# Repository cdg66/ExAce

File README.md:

# 📘 Project ExAce

> [!Warning]
>
> Content is not proven and suject to change without notice! Send to fab at your own risk. 

## 🧩 Overview

A tiny yet powerful fpga acceleration card designed with the Framework laptop expansion module system in mind.

## 🛠️ Features

- ✅ [CCGM1A1/2/4 compatible](https://colognechip.com/docs/ds1001-gatemate1-datasheet-latest.pdf)
- ✅ 20,480, 40,960 or 81,920 8-input LUT-trees.
- ✅ USB-type C, 5V 1.5A.
- ✅ Full access to SERDES via the USB-c connector (1 for A1/A2 and 2 for A4 device).
- ✅ USB2.0 interface is shared between the fpga and mcu via a USB mux.
- ✅ STM32L422RBI6 coprocessor and programmer.
- ✅ Shared Earth and i2c between the fpga and microcontroller for easier development.
- ✅ Free and Open-source FPGA toolchain!
- ✅ Lots of sensors!: PDM microphone, 6DoF imu, magnetometer, and thermometer.
- ✅ 8 user programmable led ideal for VU meters.
- ✅ 1 lvds IO ideal for connecting multiple board together in a cluster.
- 🔜 TinyFPGA-Bootloader support TBD.
- 🔜 DirtyJTAG support TBD.

---

## 💪 Application

- ✅ Machine learning
- ✅ Simulation
- ✅ Audio/Signal processing
- ✅ Retro Gaming
- ✅ Development platform

## 🗂️ Repository Structure

```bash
📁 /pcb-project-root
├── /3D_Models                    # 3D models of the PCB rendering
├── /Outputs/Fabrication          # Generated Gerber files, BOM and POS for fabrication
├── /PINOUT                       # STM32CubeMx for reference pinout
├── /Testbench/ExAceTestbench     # Testbench to break out serdes signals
├── /.gitignore
└── README.md
```

---

## 🧰 Tools & Dependencies

- **Design Software:** KiCad (v9.0.2 or higher)
- **MCU/FPGA Programmer:** ST-Link,Pico Dirty JTAG
- **Firmware Toolchain:** STM32CubeMX, arm toolchain, [Colonge chip open source toolchain](https://www.colognechip.com/docs/ug1002-toolchain-install-latest.pdf)  

---

## 🖼️ 3D view

---

## 🏗️ Getting Started

1. **Clone this repository**
   ```bash
   git clone https://github.com/cdg66/ExAce.git
   ```
2. **Open the project** in KiCad (navigate to `Expansion_Card_Retrofit.kicad_pro`)
3. **Modify / Build / Export Gerbers**

---

## 🚀 Fabrication

To get the board fabricated:

- Use the files in the `/Outputs` directory
- Recommended fabs:
  - [NextPcb](https://www.nextpcb.com/)
  - [JLCPCB](https://jlcpcb.com/) 

Stack-up:

The recommended stack up is the JLC08081H-1080A at JLCPCB but can be done at any other PCB manufacturer.

---

## 🔧 License

This work is licensed under a [Creative Commons Attribution 4.0 International License](https://creativecommons.org/licenses/by/4.0/).

This project references and builds upon the open-source designs from  
[FrameworkComputer/ExpansionCards](https://github.com/FrameworkComputer/ExpansionCards),  
which is also licensed under the [Creative Commons Attribution 4.0 International License (CC-BY-4.0)](https://creativecommons.org/licenses/by/4.0/).

TPSM82822SILR

Footprint: Ultralibrarian

3D model: SnapMagic

Edited by me

S3A2505-100.000-L-X1-R

Symbol, Footprint, 3D model: SnapMagic

Edited by me

1054440011

3D model: Molex

KXT_331_LHS

3D model: SnapMagic

STM32L422RBI6

3D model: SnapMagic

TPS7A2033PDQNR

3D model: SnapMagic

---

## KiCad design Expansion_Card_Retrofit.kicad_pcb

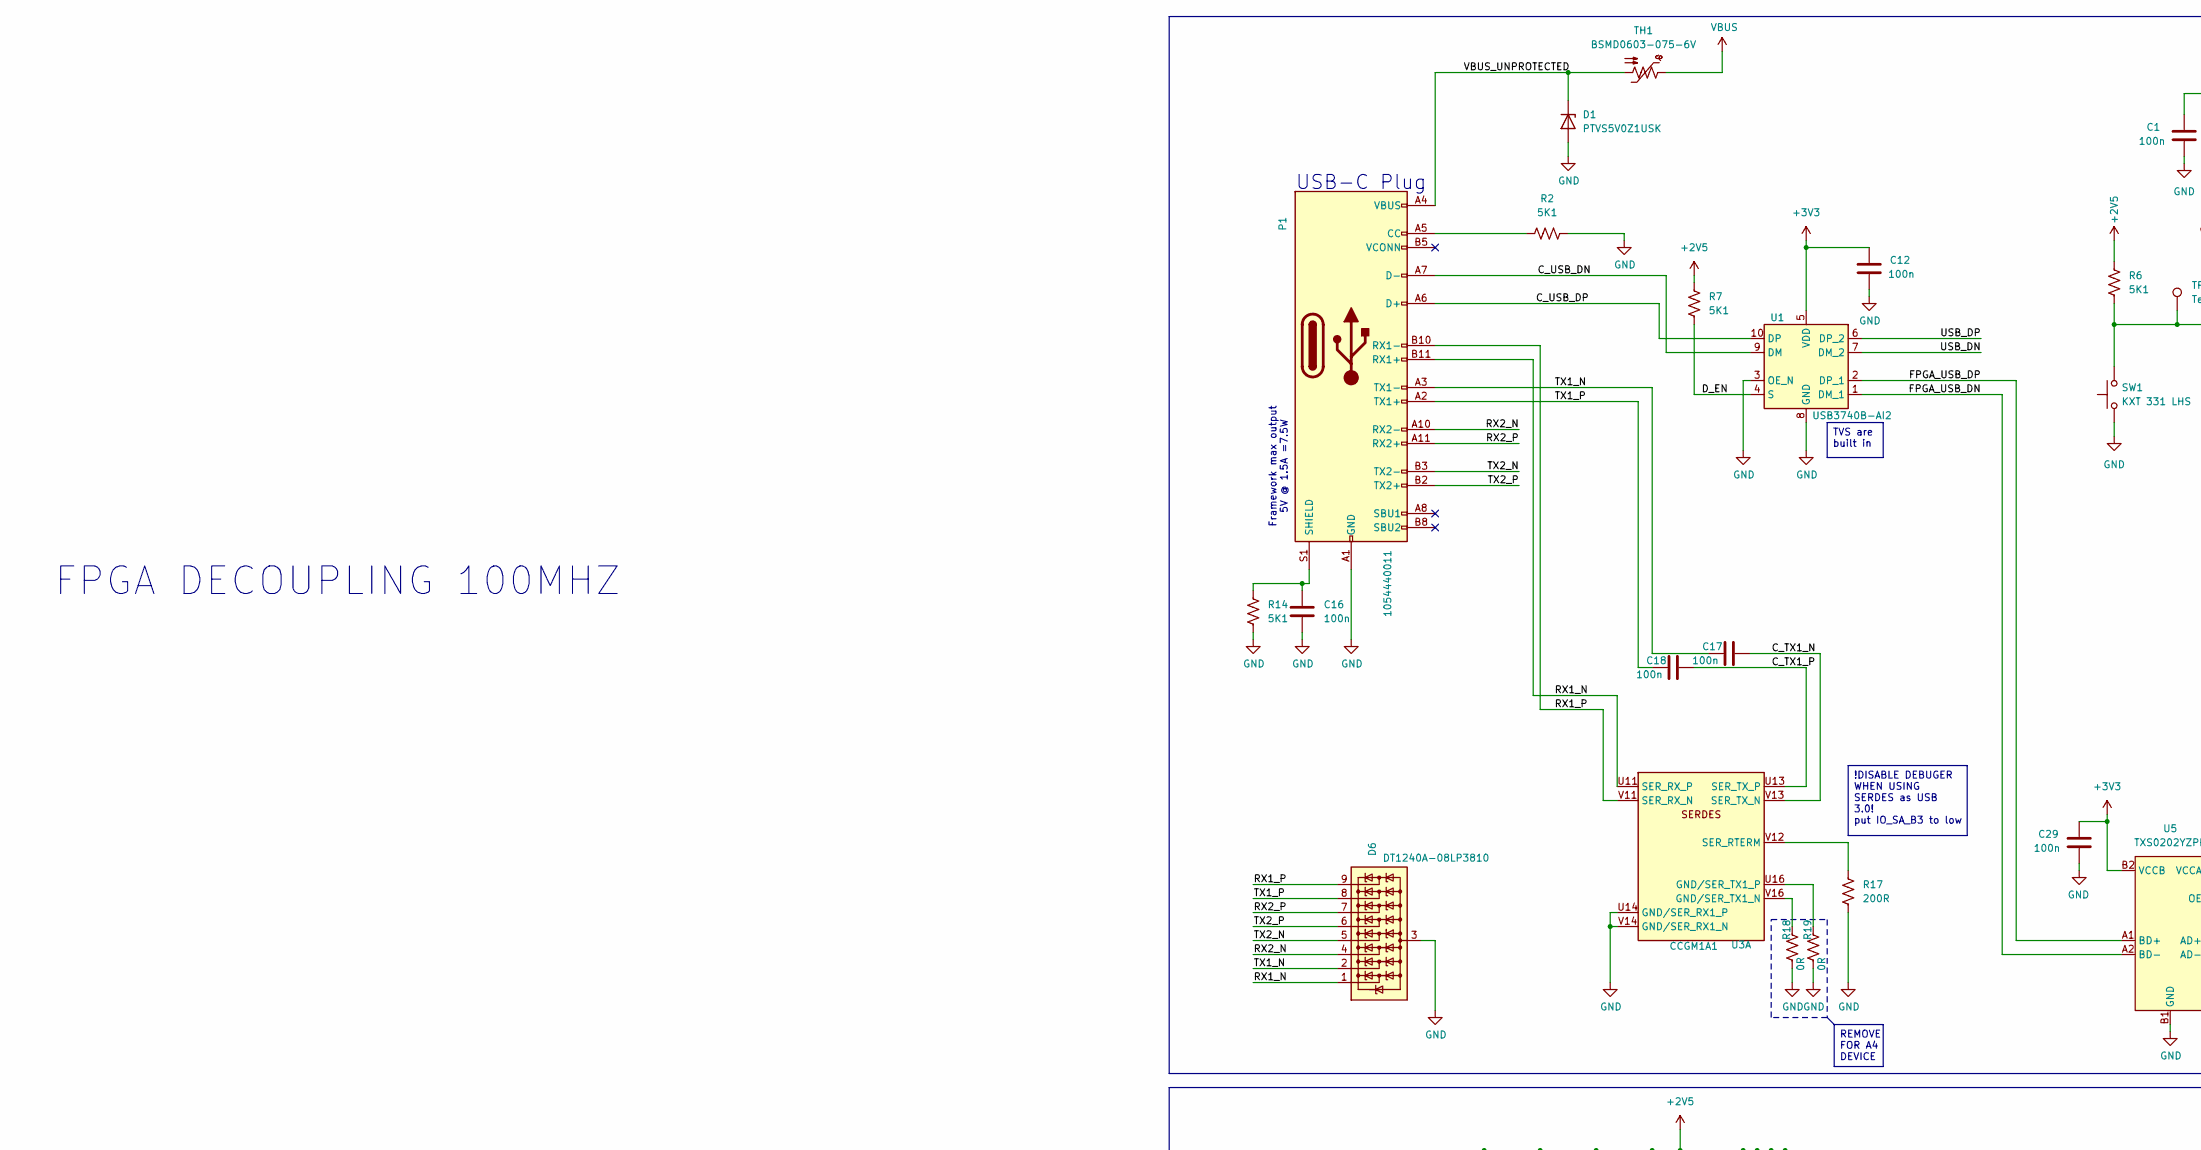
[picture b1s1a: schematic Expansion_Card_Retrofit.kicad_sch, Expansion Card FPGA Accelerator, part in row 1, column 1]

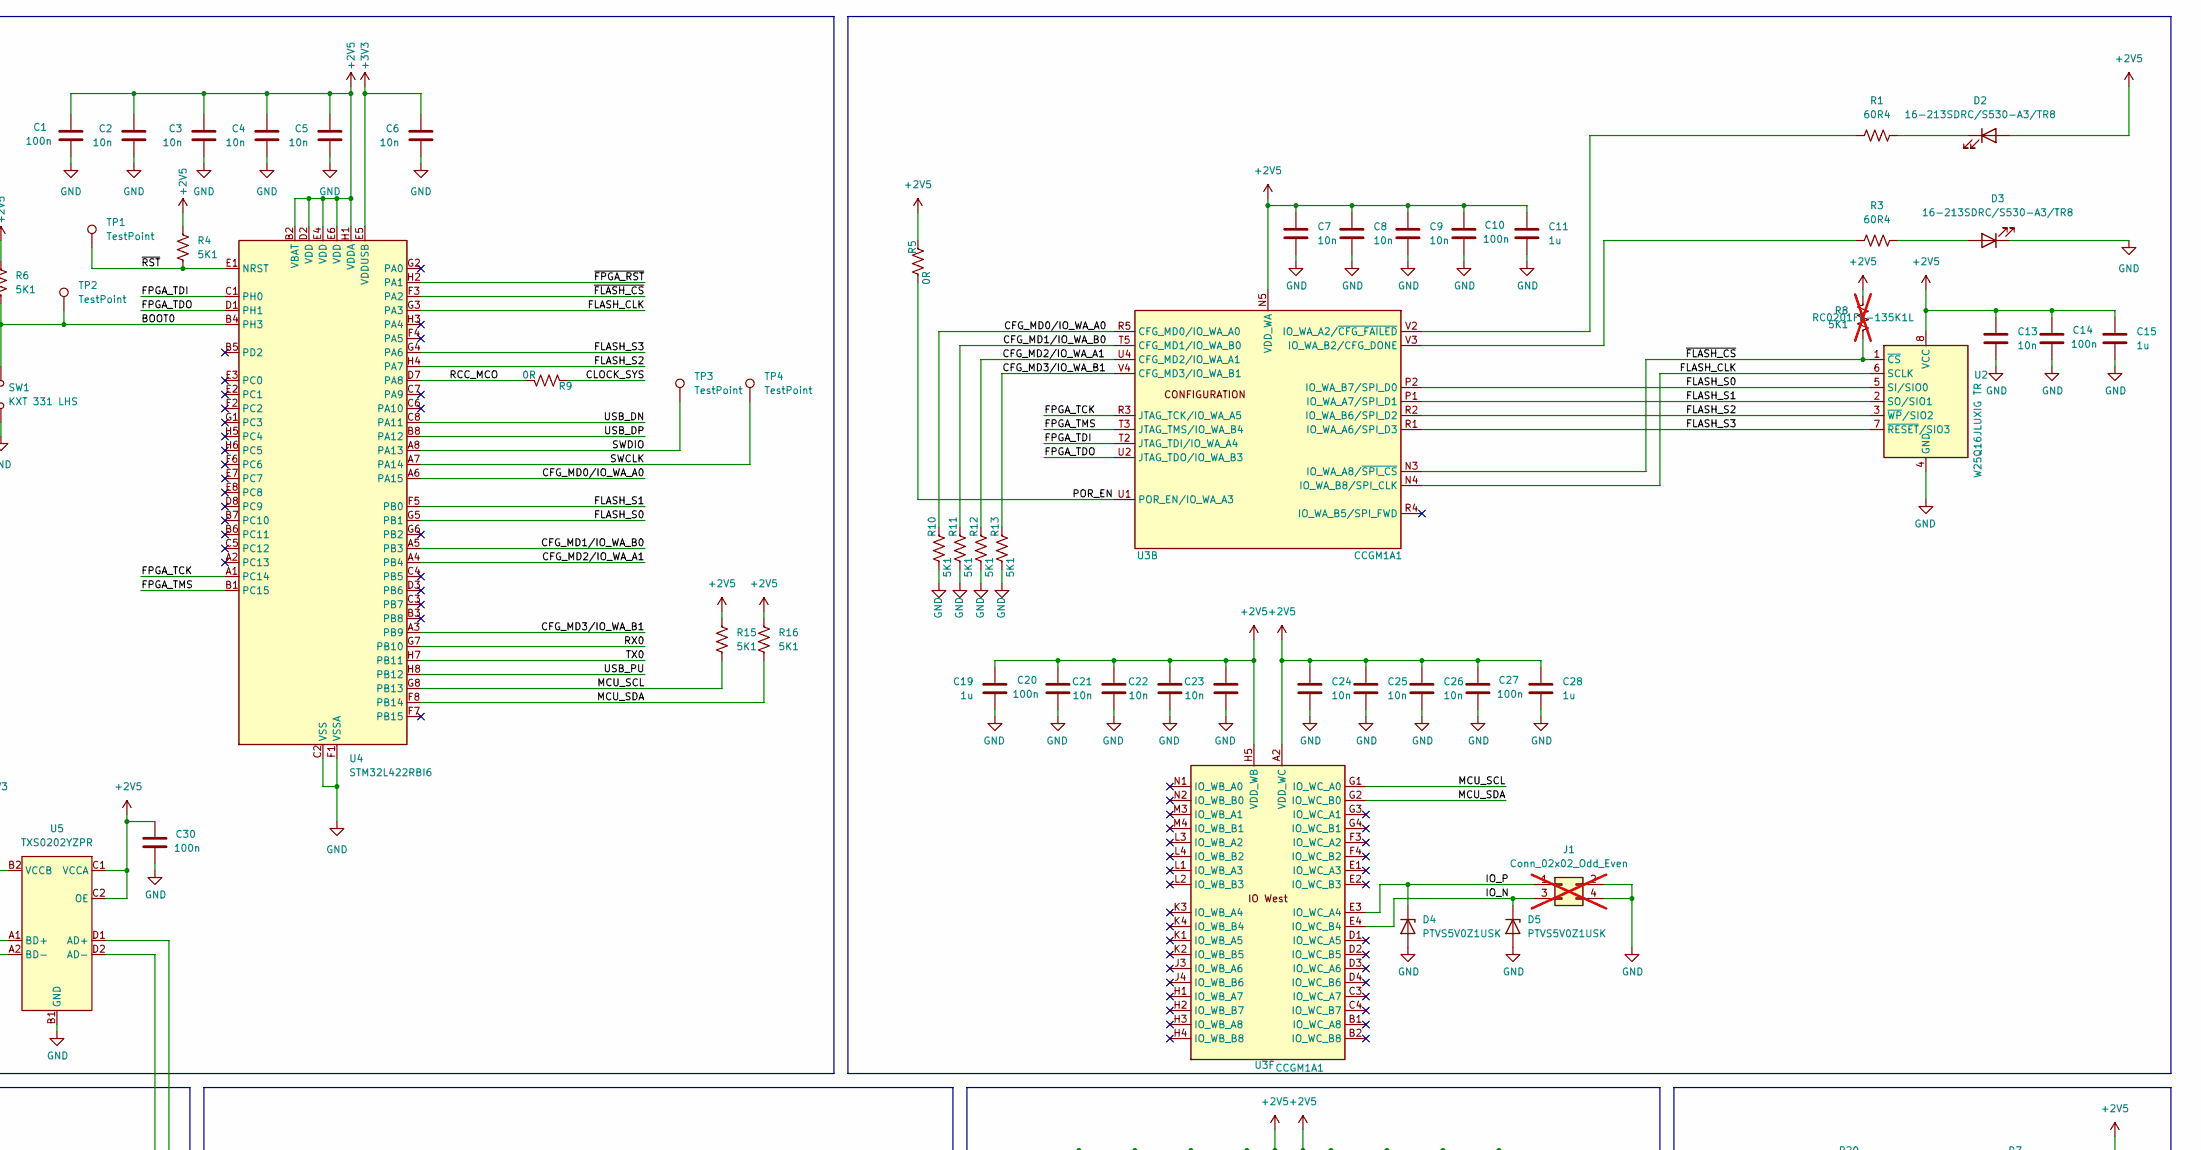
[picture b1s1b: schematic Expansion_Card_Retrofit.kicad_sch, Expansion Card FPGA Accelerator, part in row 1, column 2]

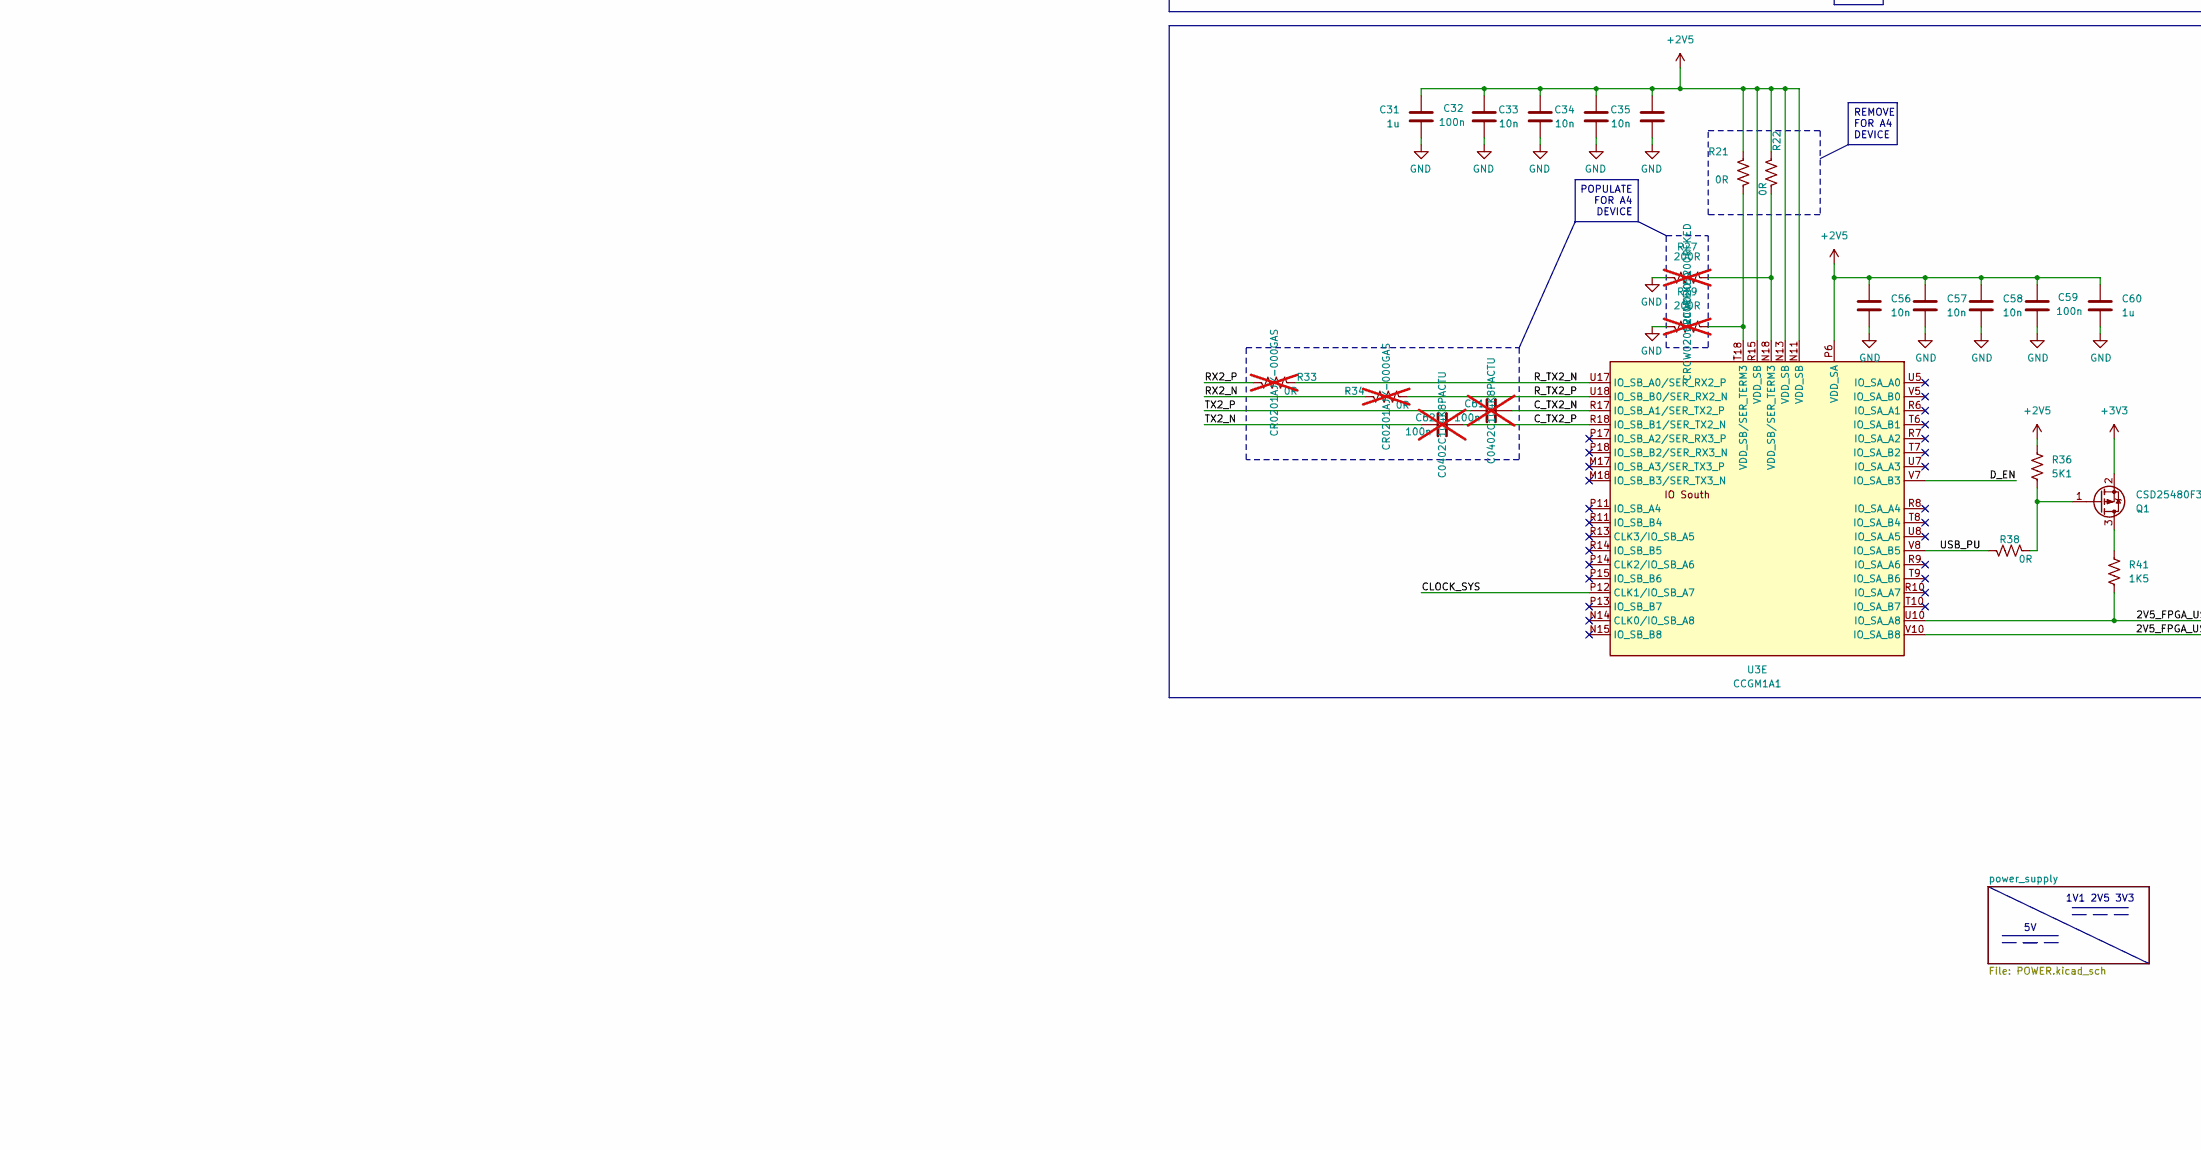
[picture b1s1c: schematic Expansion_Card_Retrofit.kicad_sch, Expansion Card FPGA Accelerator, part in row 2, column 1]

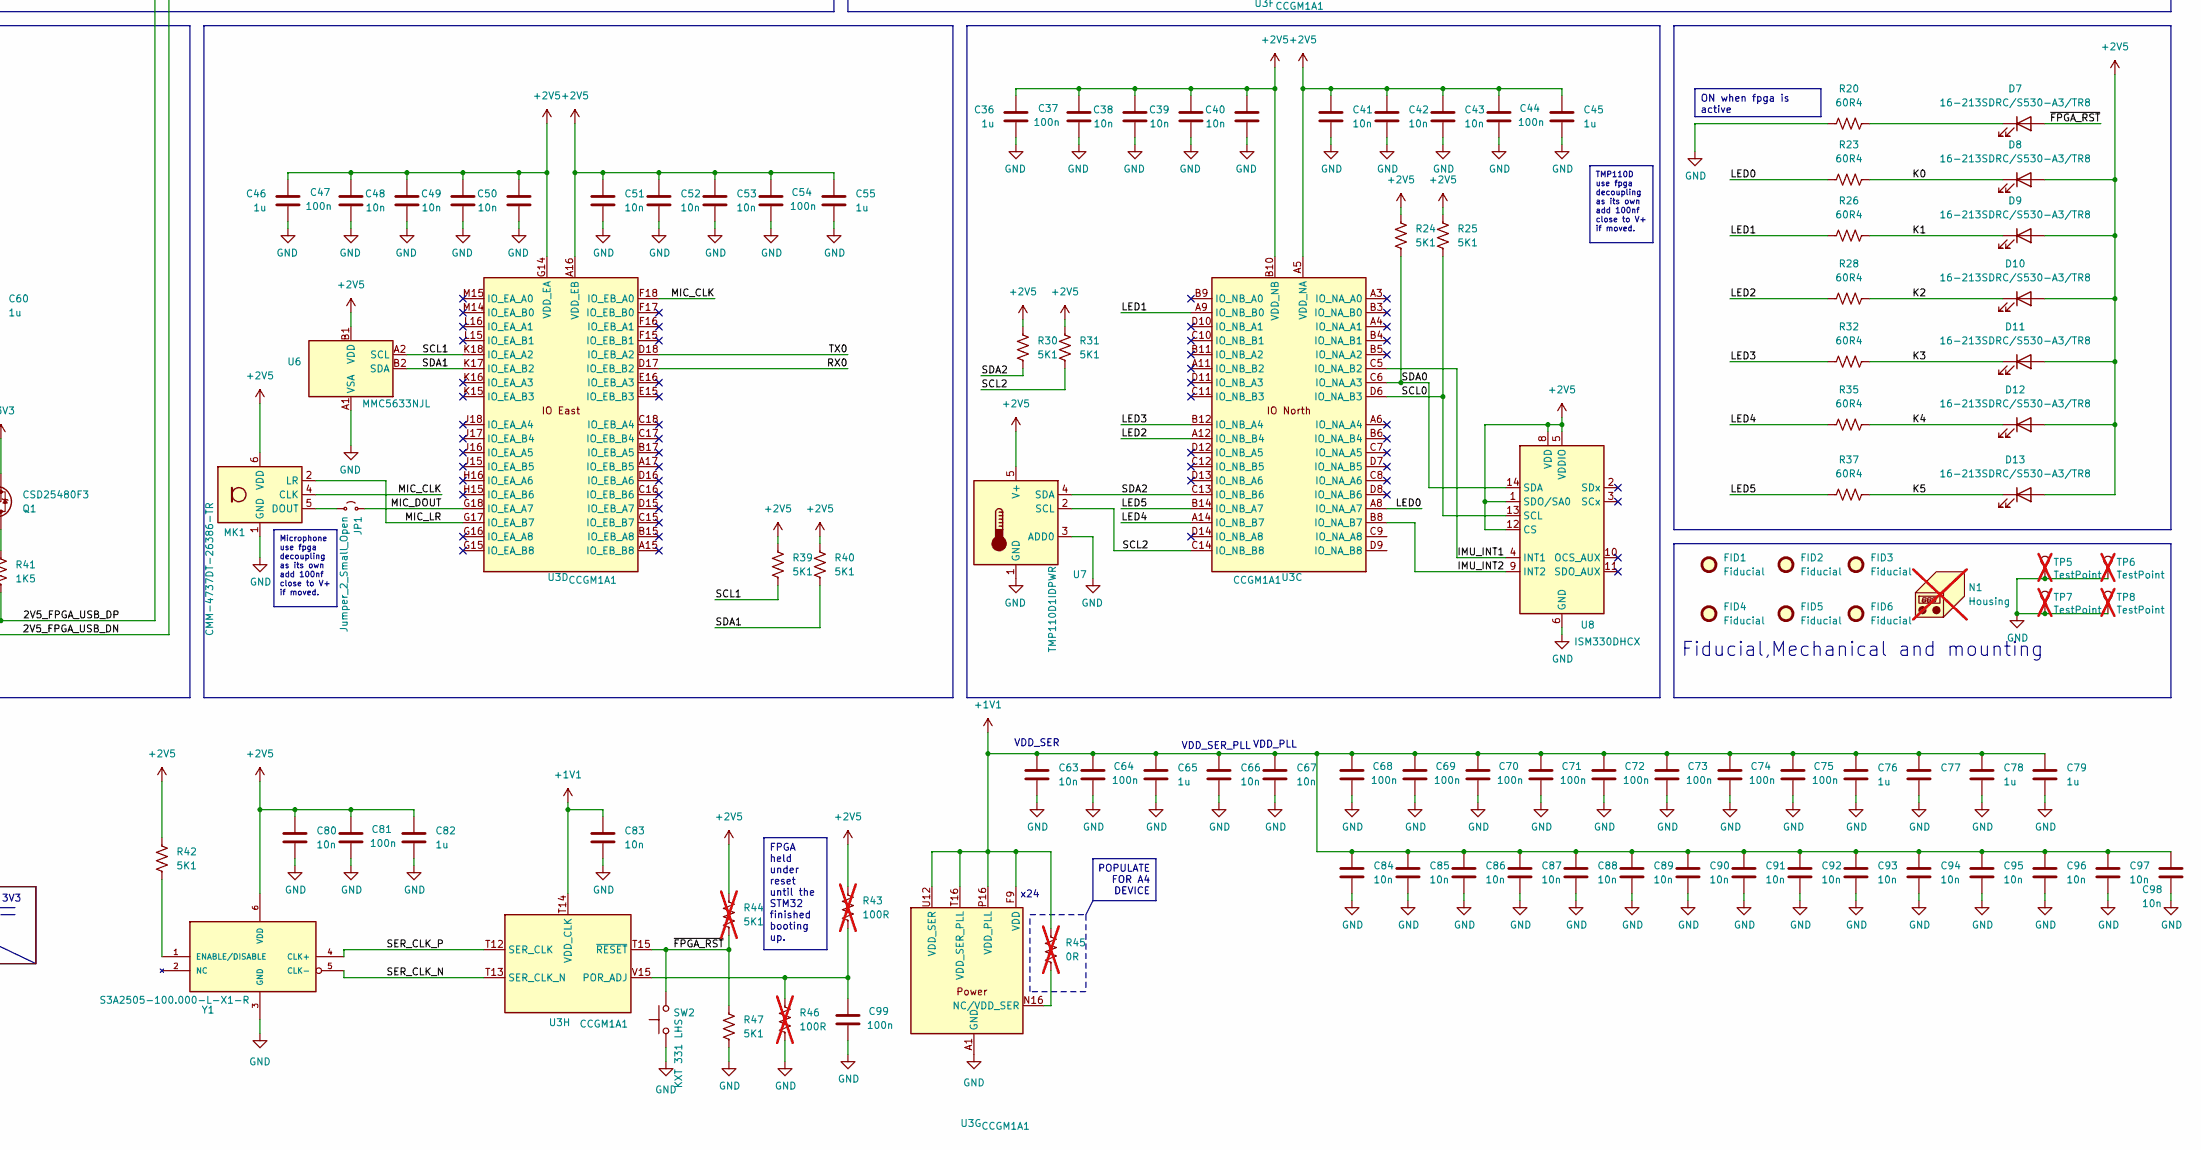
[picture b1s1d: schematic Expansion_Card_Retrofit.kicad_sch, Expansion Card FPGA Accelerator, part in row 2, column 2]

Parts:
C1, C10, C12, C14, C16, C17, C18, C20, C27, C29, C30, C32, C37, C44, C47, C54, C59, C64, C68, C69, C70, C71, C72, C73, C74, C75, C81, C99: 100n; C_0402_1005Metric; MPN C0402C104K8PACTU
C2, C3, C4, C5, C6, C7, C8, C9, C13, C21, C22, C23, C24, C25, C26, C33, C34, C35, C38, C39, C40, C41, C42, C43, C48, C49, C50, C51, C52, C53, C56, C57, C58, C63, C66, C67, C80, C83, C84, C85, C86, C87, C88, C89, C90, C91, C92, C93, C94, C95, C96, C97, C98: 10n; C_0201_0603Metric; MPN C0201C103K4PACTU
C11, C15, C19, C28, C31, C36, C45, C46, C55, C60, C65, C76, C77, C78, C79, C82: 1u; C_0402_1005Metric; MPN CL05A105KA5NQNC
C61, C62: 100n; C_0402_1005Metric; MPN C0402C104K8PACTU; not fitted
D1, D4, D5: PTVS5V0Z1USK; Nexperia_DSN1608-2_1.6x0.8mm; MPN PTVS5V0Z1USKYL
D2, D3, D7, D8, D9, D10, D11, D12, D13: 16-213SDRC/S530-A3/TR8; LED_0402_1005Metric; MPN 16-213SDRC/S530-A3/TR8
D6: DT1240A-08LP3810; UDFN-9_1.0x3.8mm_P0.5mm; MPN DT1240A-08LP3810
FID1, FID2, FID3, FID4, FID5, FID6: Fiducial; Fiducial_0.5mm_Mask1mm; MPN DNP
J1: Conn_02x02_Odd_Even; PinHeader_2x02_P1.00mm_Horizontal; MPN DNP; not fitted
JP1: Jumper_2_Small_Open; Jumper_open; MPN DNP
MK1: CMM-4737DT-26386-TR; ST_HLGA-6_3.76x4.72mm_P1.65mm; MPN CMM-4737DT-26386-TR
N1: Housing; Enclosure; MPN DNP; not fitted
P1: 1054440011; USB_C_Plug_Molex_105444; MPN 1054440011
Q1: CSD25480F3; Texas_PicoStar_DFN-3_0.69x0.60mm; MPN CSD25480F3
R1, R3, R20, R23, R26, R28, R32, R35, R37: 60R4; R_0201_0603Metric; MPN RC0201FR-0760R4L
R2, R4, R6, R7, R10, R11, R12, R13, R14, R15, R16, R24, R25, R30, R31, R36, R39, R40, R42, R47: 5K1; R_0201_0603Metric; MPN RC0201FR-135K1L
R5, R9, R18, R19, R21, R22, R38: 0R; R_0201_0603Metric; MPN CR0201AJ/-000GAS
R8, R44: 5K1; R_0201_0603Metric; MPN RC0201FR-135K1L; not fitted
R17: 200R; R_0201_0603Metric; MPN CRCW0201200RFKED
R27, R29: 200R; R_0201_0603Metric; MPN CRCW0201200RFKED; not fitted
R33, R34, R45: 0R; R_0201_0603Metric; MPN CR0201AJ/-000GAS; not fitted
R41: 1K5; R_0201_0603Metric; MPN RC0201FR-071K5L
R43, R46: 100R; R_0201_0603Metric; MPN RC0201FR-07100RL; not fitted
SW1, SW2: KXT 331 LHS; SW_SPST_CK_KXT3; MPN KXT 331 LHS
TH1: BSMD0603-075-6V; C_0603_1608Metric; MPN PTSLR06038V075
TP1, TP2, TP3, TP4: TestPoint; TestPoint_Pad_D1.0mm; MPN DNP
TP5, TP6, TP7, TP8: TestPoint; TestPoint_Pad_1.5x1.5mm; MPN DNP; not fitted
U1: USB3740B-AI2; UQFN-10_1.3x1.8mm_P0.4mm; MPN USB3740B-AI2-TR
U2: W25Q16JLUXIG TR; Winbond_USON-8-1EP_3x2mm_P0.5mm_EP0.2x1.6mm; MPN W25Q32RVXHJQ TR
U3: CCGM1A1; BGA-324_15.0x15.0mm_Layout18x18_P0.8mm_Ball0.45mm_Pad0.4mm_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; MPN CCGM1A1-BGA324
U4: STM32L422RBI6; UFBGA-64_5x5mm_Layout8x8_P0.5mm; MPN STM32L422RBI6
U5: TXS0202YZPR; Texas_DSBGA-8_0.9x1.9mm_Layout2x4_P0.5mm; MPN TXS0202YZPR
U6: MMC5633NJL; WLP-4_0.86x0.86mm_P0.4mm; MPN MMC5633NJL
U7: TMP110D1IDPWR; Texas_X2SON-5_0.8x0.8mm_P0.48mm; MPN TMP110D
U8: ISM330DHCX; LGA-14_3x2.5mm_P0.5mm_LayoutBorder3x4y; MPN ISM330DHCXTR
Y1: S3A2505-100.000-L-X1-R; OSC_S3A2505-100.000-L-X1-R; PARTREV April 16,2024

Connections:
+1V1: C63.1, C64.1, C65.1, C66.1, C67.1, C68.1, C69.1, C70.1, C71.1, C72.1, C73.1, C74.1, C75.1, C76.1, C77.1, C78.1, C79.1, C83.1, C84.1, C85.1, C86.1, C87.1, C88.1, C89.1, C90.1, C91.1, C92.1, C93.1, C94.1, C95.1, C96.1, C97.1, C98.1, R45.1, U3.F9 (VDD), U3.G6 (VDD), U3.G8 (VDD), U3.G10 (VDD), U3.G12 (VDD), U3.H7 (VDD), U3.H9 (VDD), U3.H11 (VDD), U3.H13 (VDD), U3.J6 (VDD), U3.J8 (VDD), U3.J10 (VDD), U3.J12 (VDD), U3.K7 (VDD), U3.K9 (VDD), U3.K11 (VDD), U3.K13 (VDD), U3.L6 (VDD), U3.L8 (VDD), U3.L10 (VDD), U3.L12 (VDD), U3.M7 (VDD), U3.M9 (VDD), U3.M11 (VDD), U3.M13 (VDD), U3.N6 (VDD), U3.N8 (VDD), U3.N10 (VDD), U3.P16 (VDD_PLL), U3.T14 (VDD_CLK), U3.T16 (VDD_SER_PLL), U3.U12 (VDD_SER), U3.V17 (VDD_SER); also elsewhere on the board
+2V5: C1.1, C2.1, C3.1, C4.1, C5.1, C7.1, C8.1, C9.1, C10.1, C11.1, C13.1, C14.1, C15.1, C19.1, C20.1, C21.1, C22.1, C23.1, C24.1, C25.1, C26.1, C27.1, C28.1, C30.1, C31.1, C32.1, C33.1, C34.1, C35.1, C36.1, C37.1, C38.1, C39.1, C40.1, C41.1, C42.1, C43.1, C44.1, C45.1, C46.1, C47.1, C48.1, C49.1, C50.1, C51.1, C52.1, C53.1, C54.1, C55.1, C56.1, C57.1, C58.1, C59.1, C60.1, C80.1, C81.1, C82.1, D2.2 (A), D8.2 (A), D9.2 (A), D10.2 (A), D11.2 (A), D12.2 (A), D13.2 (A), MK1.6 (VDD), R4.1, R5.1, R6.1, R7.1, R8.1, R15.1, R16.1, R21.1, R22.1, R24.1, R25.1, R30.1, R31.1, R36.2, R39.1, R40.1, R42.1, R43.1, R44.1, U2.8 (VCC), U3.A2 (VDD_WC), U3.A5 (VDD_NA), U3.A16 (VDD_EB), U3.B7 (VDD_NA), U3.B10 (VDD_NB), U3.B13 (VDD_NB), U3.B18 (VDD_EB), U3.C2 (VDD_WC), U3.D5 (VDD_WC), U3.E6 (VDD_NA), U3.E8 (VDD_NA), U3.E10 (VDD_NB), U3.E12 (VDD_NB), U3.E14 (VDD_EB), U3.E17 (VDD_EB), U3.F2 (VDD_WC), U3.F5 (VDD_WC), U3.F7 (VDD_NA), U3.F11 (VDD_NB), U3.F13 (VDD_EB), U3.G14 (VDD_EA), U3.H5 (VDD_WB), U3.H17 (VDD_EA), U3.J2 (VDD_WB), U3.J14 (VDD_EA), U3.K5 (VDD_WB), U3.L14 (VDD_EA), U3.L17 (VDD_EA), U3.M2 (VDD_WB), U3.M5 (VDD_WB), U3.N5 (VDD_WA), U3.N11 (VDD_SB), U3.N13 (VDD_SB), U3.P3 (VDD_WA), U3.P5 (VDD_WA), U3.P6 (VDD_SA), U3.P8 (VDD_SA), U3.P10 (VDD_SA), U3.R15 (VDD_SB), U3.T1 (VDD_WA), U3.U3 (VDD_WA), U3.U6 (VDD_SA), U3.U9 (VDD_SA), U4.B2 (VBAT), U4.D2 (VDD), U4.E4 (VDD), U4.E6 (VDD), U4.H1 (VDDA), U5.C1 (VCCA), U5.C2 (OE), U6.B1 (VDD), U7.5 (V+), U8.1 (SDO/SA0), U8.5 (VDDIO), U8.8 (VDD), U8.12 (CS), Y1.6 (VDD); also elsewhere on the board
+3V3: C6.1, C12.1, C29.1, Q1.2 (S), U1.5 (VDD), U4.E5 (VDDUSB), U5.B2 (VCCB); also elsewhere on the board
/2V5_FPGA_USB_DN: U3.V10 (IO_SA_B8), U5.D1 (AD+)
/2V5_FPGA_USB_DP: R41.2, U3.U10 (IO_SA_A8), U5.D2 (AD-)
/BOOT0: R6.2, SW1.2, TP2.1, U4.B4 (PH3)
/CFG_MD0/IO_WA_A0: R10.1, U3.R5 (CFG_MD0/IO_WA_A0), U4.A6 (PA15)
/CFG_MD1/IO_WA_B0: R11.1, U3.T5 (CFG_MD1/IO_WA_B0), U4.A5 (PB3)
/CFG_MD2/IO_WA_A1: R12.1, U3.U4 (CFG_MD2/IO_WA_A1), U4.A4 (PB4)
/CFG_MD3/IO_WA_B1: R13.1, U3.V4 (CFG_MD3/IO_WA_B1), U4.A3 (PB9)
/CLOCK_SYS: R9.1, U3.P12 (CLK1/IO_SB_A7)
/C_TX1_N: C17.2, U3.V13 (SER_TX_N)
/C_TX1_P: C18.2, U3.U13 (SER_TX_P)
/C_TX2_N: C61.2, U3.R17 (IO_SB_A1/SER_TX2_P)
/C_TX2_P: C62.2, U3.R18 (IO_SB_B1/SER_TX2_N)
/C_USB_DN: P1.A7 (D-), U1.9 (DM)
/C_USB_DP: P1.A6 (D+), U1.10 (DP)
/D_EN: R7.2, U1.4 (S), U3.V7 (IO_SA_B3)
/FLASH_CLK: U2.6 (SCLK), U3.N4 (IO_WA_B8/SPI_CLK), U4.G3 (PA3)
/FLASH_S0: U2.5 (SI/SIO0), U3.P2 (IO_WA_B7/SPI_D0), U4.G5 (PB1)
/FLASH_S1: U2.2 (SO/SIO1), U3.P1 (IO_WA_A7/SPI_D1), U4.F5 (PB0)
/FLASH_S2: U2.3 (~WP/SIO2), U3.R2 (IO_WA_B6/SPI_D2), U4.H4 (PA7)
/FLASH_S3: U2.7 (~RESET/SIO3), U3.R1 (IO_WA_A6/SPI_D3), U4.G4 (PA6)
/FPGA_TCK: U3.R3 (JTAG_TCK/IO_WA_A5), U4.A1 (PC14)
/FPGA_TDI: U3.T2 (JTAG_TDI/IO_WA_A4), U4.C1 (PH0)
/FPGA_TDO: U3.U2 (JTAG_TDO/IO_WA_B3), U4.D1 (PH1)
/FPGA_TMS: U3.T3 (JTAG_TMS/IO_WA_B4), U4.B1 (PC15)
/FPGA_USB_DN: U1.1 (DM_1), U5.A2 (BD-)
/FPGA_USB_DP: U1.2 (DP_1), U5.A1 (BD+)
/IMU_INT1: U3.C5 (IO_NA_B2), U8.4 (INT1)
/IMU_INT2: U3.B8 (IO_NA_B7), U8.9 (INT2)
/IO_N: D5.1 (K), J1.3, U3.E4 (IO_WC_B4)
/IO_P: D4.1 (K), J1.1, U3.E3 (IO_WC_A4)
/K0: D8.1 (K), R23.2
/K1: D9.1 (K), R26.2
/K2: D10.1 (K), R28.2
/K3: D11.1 (K), R32.2
/K4: D12.1 (K), R35.2
/K5: D13.1 (K), R37.2
/LED0: R23.1, U3.A8 (IO_NA_A7)
/LED1: R26.1, U3.A9 (IO_NB_B0)
/LED2: R28.1, U3.A12 (IO_NB_B4)
/LED3: R32.1, U3.B12 (IO_NB_A4)
/LED4: R35.1, U3.A14 (IO_NB_B7)
/LED5: R37.1, U3.B14 (IO_NB_A7)
/MCU_SCL: R15.2, U3.G1 (IO_WC_A0), U4.G8 (PB13)
/MCU_SDA: R16.2, U3.G2 (IO_WC_B0), U4.F8 (PB14)
/MIC_CLK: MK1.4 (CLK), U3.F18 (IO_EB_A0)
/MIC_DOUT: JP1.2 (B), U3.G18 (IO_EA_A7)
/MIC_LR: MK1.2 (LR), U3.G17 (IO_EA_B7)
/POR_EN: R5.2, U3.U1 (POR_EN/IO_WA_A3)
/RCC_MCO: R9.2, U4.D7 (PA8)
/RX0: U3.D17 (IO_EB_B2), U4.G7 (PB10)
/RX1_N: D6.1 (K1), P1.B11 (RX1+), U3.U11 (SER_RX_P)
/RX1_P: D6.9 (K8), P1.B10 (RX1-), U3.V11 (SER_RX_N)
/RX2_N: D6.4 (K3), P1.A10 (RX2-), R34.1
/RX2_P: D6.7 (K6), P1.A11 (RX2+), R33.1
/R_TX2_N: R33.2, U3.U17 (IO_SB_A0/SER_RX2_P)
/R_TX2_P: R34.2, U3.U18 (IO_SB_B0/SER_RX2_N)
/SCL0: R25.2, U3.D6 (IO_NA_B3), U8.13 (SCL)
/SCL1: R39.2, U3.K18 (IO_EA_A2), U6.A2 (SCL)
/SCL2: R31.2, U3.C14 (IO_NB_B8), U7.2 (SCL)
/SDA0: R24.2, U3.C6 (IO_NA_A3), U8.14 (SDA)
/SDA1: R40.2, U3.K17 (IO_EA_B2), U6.B2 (SDA)
/SDA2: R30.2, U3.C13 (IO_NB_B6), U7.4 (SDA)
/SER_CLK_N: U3.T13 (SER_CLK_N), Y1.5 (CLK-)
/SER_CLK_P: U3.T12 (SER_CLK), Y1.4 (CLK+)
/SWCLK: TP4.1, U4.A7 (PA14)
/SWDIO: TP3.1, U4.A8 (PA13)
/TX0: U3.D18 (IO_EB_A2), U4.H7 (PB11)
/TX1_N: C17.1, D6.2 (K2), P1.A3 (TX1-)
/TX1_P: C18.1, D6.8 (K7), P1.A2 (TX1+)
/TX2_N: C62.1, D6.5 (K4), P1.B3 (TX2-)
/TX2_P: C61.1, D6.6 (K5), P1.B2 (TX2+)
/USB_DN: U1.7 (DM_2), U4.C8 (PA11)
/USB_DP: U1.6 (DP_2), U4.B8 (PA12)
/USB_PU: R38.1, U3.V8 (IO_SA_B5), U4.H8 (PB12)
/VBUS_UNPROTECTED: D1.1 (K), P1.A4 (VBUS), P1.A9 (VBUS), P1.B4 (VBUS), P1.B9 (VBUS), TH1.2
/~FLASH_CS: R8.2, U2.1 (~CS), U3.N3 (IO_WA_A8/~SPI_CS), U4.F3 (PA2)
/~FPGA_RST: D7.2 (A), R44.2, R47.1, SW2.2, U3.T15 (~RESET), U4.H2 (PA1)
/~RST: R4.2, TP1.1, U4.E1 (NRST)
GND: C1.2, C2.2, C3.2, C4.2, C5.2, C6.2, C7.2, C8.2, C9.2, C10.2, C11.2, C12.2, C13.2, C14.2, C15.2, C16.2, C19.2, C20.2, C21.2, C22.2, C23.2, C24.2, C25.2, C26.2, C27.2, C28.2, C29.2, C30.2, C31.2, C32.2, C33.2, C34.2, C35.2, C36.2, C37.2, C38.2, C39.2, C40.2, C41.2, C42.2, C43.2, C44.2, C45.2, C46.2, C47.2, C48.2, C49.2, C50.2, C51.2, C52.2, C53.2, C54.2, C55.2, C56.2, C57.2, C58.2, C59.2, C60.2, C63.2, C64.2, C65.2, C66.2, C67.2, C68.2, C69.2, C70.2, C71.2, C72.2, C73.2, C74.2, C75.2, C76.2, C77.2, C78.2, C79.2, C80.2, C81.2, C82.2, C83.2, C84.2, C85.2, C86.2, C87.2, C88.2, C89.2, C90.2, C91.2, C92.2, C93.2, C94.2, C95.2, C96.2, C97.2, C98.2, C99.2, D1.2 (A), D3.1 (K), D4.2 (A), D5.2 (A), D6.3 (A), J1.2, J1.4, MK1.1 (GND), MK1.3 (GND), P1.A1 (GND), P1.A12 (GND), P1.B1 (GND), P1.B12 (GND), R2.2, R10.2, R11.2, R12.2, R13.2, R14.2, R17.2, R18.2, R19.2, R20.1, R27.1, R29.1, R46.2, R47.2, SW1.1, SW2.1, TP5.1, TP6.1, TP7.1, TP8.1, U1.3 (OE_N), U1.8 (GND), U2.4 (GND), U2.9 (GND), U3.A1 (GND), U3.A7 (GND), U3.A10 (GND), U3.A13 (GND), U3.A18 (GND), U3.B16 (GND), U3.C1 (GND), U3.E5 (GND), U3.E7 (GND), U3.E9 (GND), U3.E11 (GND), U3.E13 (GND), U3.E18 (GND), U3.F1 (GND), U3.F6 (GND), U3.F8 (GND), U3.F10 (GND), U3.F12 (GND), U3.F14 (GND), U3.G5 (GND), U3.G7 (GND), U3.G9 (GND), U3.G11 (GND), U3.G13 (GND), U3.H6 (GND), U3.H8 (GND), U3.H10 (GND), U3.H12 (GND), U3.H14 (GND), U3.H18 (GND), U3.J1 (GND), U3.J5 (GND), U3.J7 (GND), U3.J9 (GND), U3.J11 (GND), U3.J13 (GND), U3.K6 (GND), U3.K8 (GND), U3.K10 (GND), U3.K12 (GND), U3.K14 (GND), U3.L5 (GND), U3.L7 (GND), U3.L9 (GND), U3.L11 (GND), U3.L13 (GND), U3.L18 (GND), U3.M1 (GND), U3.M6 (GND), U3.M8 (GND), U3.M10 (GND), U3.M12 (GND), U3.M16 (GND), U3.N7 (GND), U3.N9 (GND), U3.N12 (GND), U3.N17 (GND), U3.P4 (GND), U3.P7 (GND), U3.P9 (GND), U3.R12 (GND), U3.R16 (GND), U3.T4 (GND), U3.T11 (GND), U3.T17 (GND), U3.U14 (GND/SER_RX1_P), U3.U15 (GND), U3.V1 (GND), U3.V6 (GND), U3.V9 (GND), U3.V14 (GND/SER_RX1_N), U3.V18 (GND), U4.C2 (VSS), U4.D4 (VSS), U4.D5 (VSS), U4.D6 (VSS), U4.F1 (VSSA), U5.B1 (GND), U6.A1 (VSA), U7.1 (GND), U7.3 (ADD0), U8.6 (GND), U8.7 (GND), Y1.3 (GND); also elsewhere on the board
unnamed: D2.1 (K), R1.2
unnamed: D3.2 (A), R3.2
unnamed: D7.1 (K), R20.2
unnamed: JP1.1 (A), MK1.5 (DOUT)
unnamed: P1.A5 (CC), R2.1
unnamed: C16.1, P1.S1 (SHIELD), R14.1
unnamed: Q1.3 (D), R41.1
unnamed: Q1.1 (G), R36.1, R38.2
unnamed: R21.2, R29.2, U3.T18 (VDD_SB/SER_TERM3)
unnamed: R22.2, R27.2, U3.N18 (VDD_SB/SER_TERM3)
unnamed: R18.1, U3.V16 (GND/SER_TX1_N)
unnamed: R19.1, U3.U16 (GND/SER_TX1_P)
unnamed: R17.1, U3.V12 (SER_RTERM)
unnamed: R1.1, U3.V2 (IO_WA_A2/~CFG_FAILED)
unnamed: R3.1, U3.V3 (IO_WA_B2/CFG_DONE)
unnamed: R45.2, U3.N16 (NC/VDD_SER)
unnamed: C99.1, R43.2, R46.1, U3.V15 (POR_ADJ)
unnamed: R42.2, Y1.1 (ENABLE/DISABLE)
VBUS: TH1.1; also elsewhere on the board

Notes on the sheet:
Fiducial,Mechanical and mounting
VDD_PLL
x24
Framework max output 5V @ 1.5A =7.5W
FPGA DECOUPLING 100MHZ
USB-C Plug
1V1 2V5 3V3
VDD_SER
VDD_SER_PLL
!DISABLE DEBUGER WHEN USING SERDES as USB 3.0! put IO_SA_B3 to low
FPGA held under reset until the STM32 finished booting up.
ON when fpga is active
POPULATE FOR A4 DEVICE
Microphone use fpga decoupling as its own add 100nf close to V+ if moved.
TVS are built in
REMOVE FOR A4 DEVICE
TMP110D use fpga decoupling as its own add 100nf close to V+ if moved.

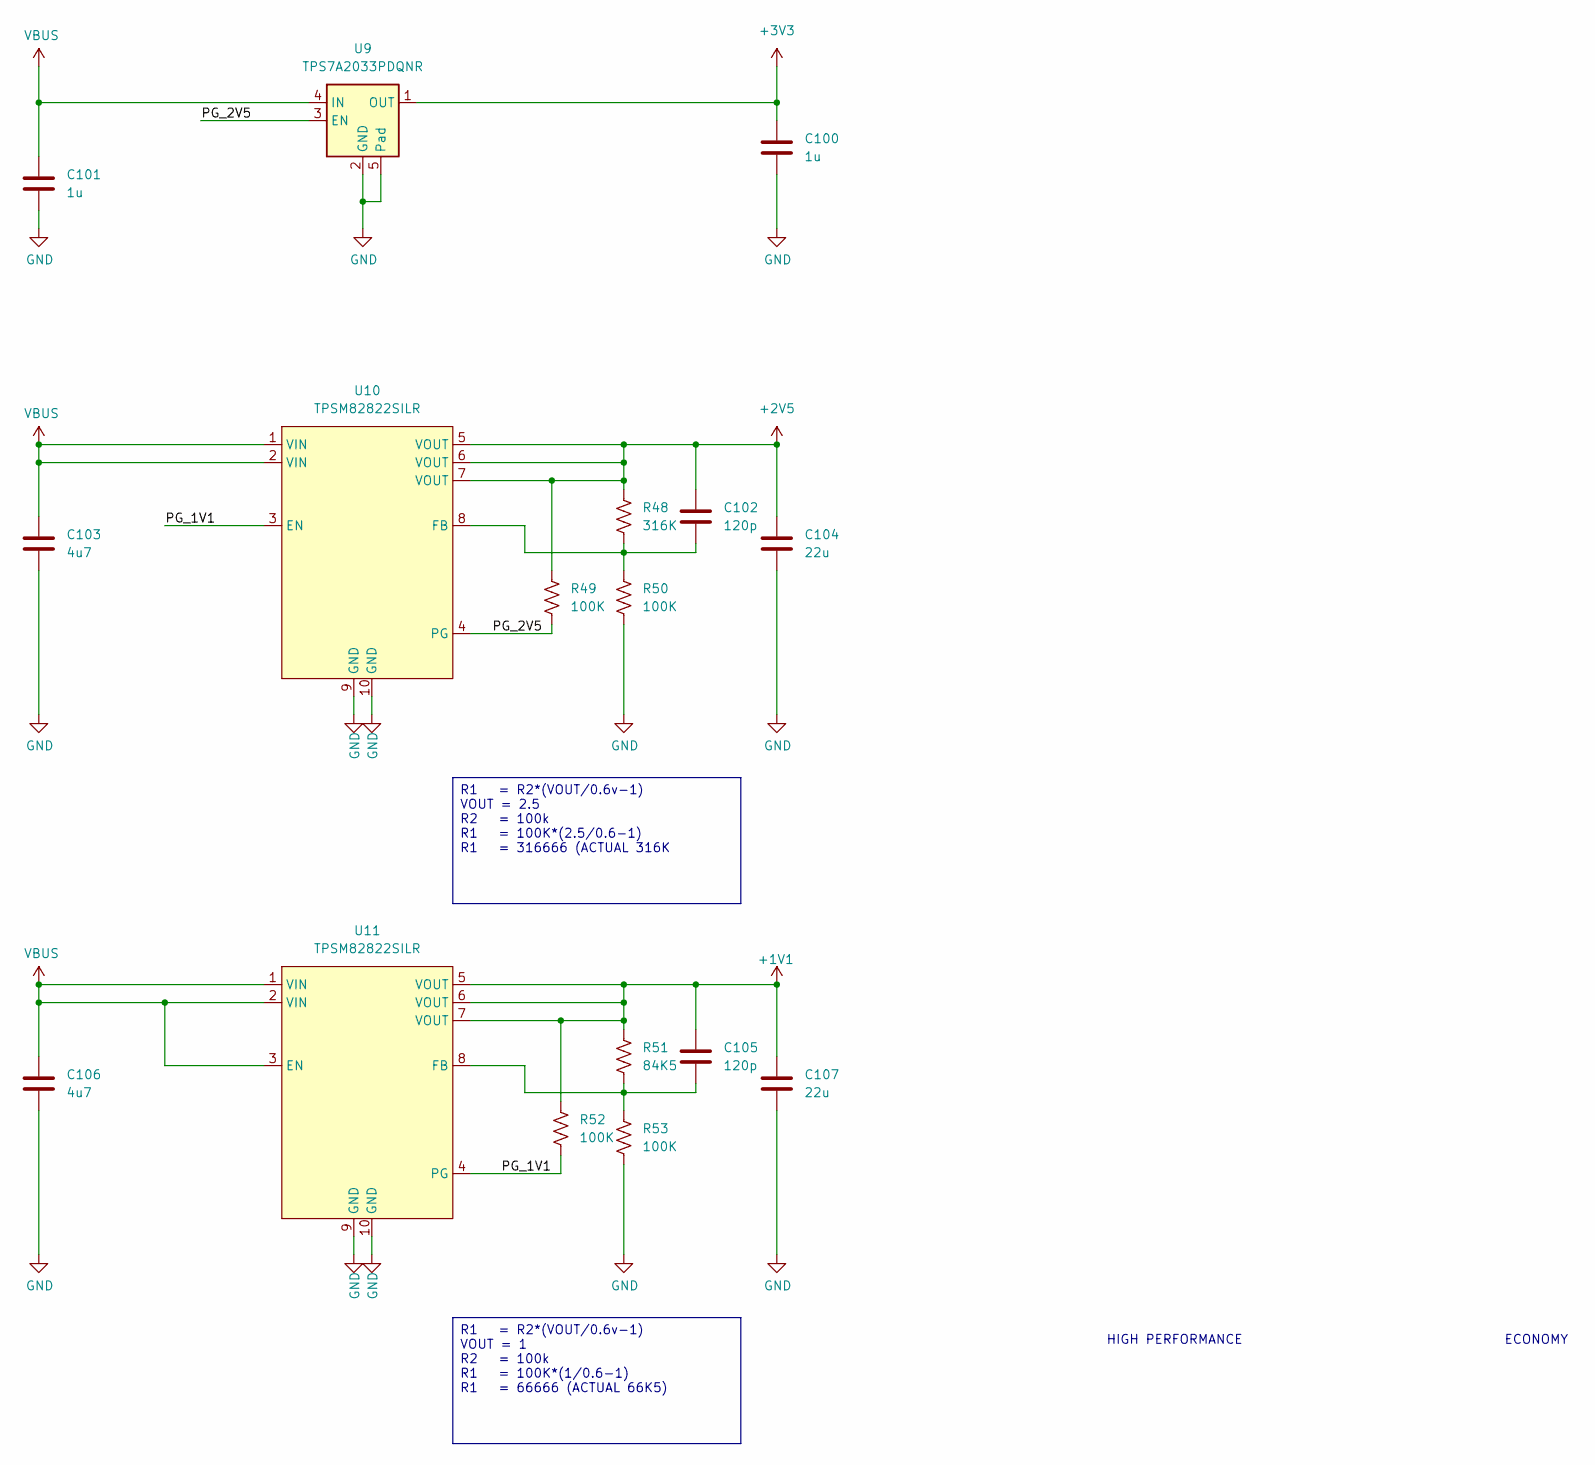
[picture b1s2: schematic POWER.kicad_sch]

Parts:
C100, C101: 1u; C_0402_1005Metric; MPN CL05A105KA5NQNC
C102, C105: 120p; C_0201_0603Metric; MPN GRM033R71E121KA01D
C103, C106: 4u7; C_0402_1005Metric; MPN GRM155C61E475ME15D
C104, C107: 22u; C_0402_1005Metric; MPN GMC04X5R226M10NT
R48: 316K; R_0201_0603Metric; MPN RC0201FR-07316KL
R49, R50, R52, R53: 100K; R_0201_0603Metric; MPN RC0201FR-07100KL
R51: 84K5; R_0201_0603Metric; MPN RC0201FR-0784K5L
U9: TPS7A2033PDQNR; Texas_X2SON-4_1x1mm_P0.65mm; MPN TPS7A2033PDQNR
U10, U11: TPSM82822SILR; SIL0010D-MFG; MPN TPSM82822SILR

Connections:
+1V1: C105.1, C107.1, R51.1, R52.1, U11.5 (VOUT), U11.6 (VOUT), U11.7 (VOUT); also elsewhere on the board
+2V5: C102.1, C104.1, R48.1, R49.1, U10.5 (VOUT), U10.6 (VOUT), U10.7 (VOUT); also elsewhere on the board
+3V3: C100.1, U9.1 (OUT); also elsewhere on the board
/power_supply/PG_1V1: R52.2, U10.3 (EN), U11.4 (PG)
/power_supply/PG_2V5: R49.2, U9.3 (EN), U10.4 (PG)
GND: C100.2, C101.2, C103.2, C104.2, C106.2, C107.2, R50.2, R53.2, U9.2 (GND), U9.5 (Pad), U10.9 (GND), U10.10 (GND), U11.9 (GND), U11.10 (GND); also elsewhere on the board
unnamed: C102.2, R48.2, R50.1, U10.8 (FB)
unnamed: C105.2, R51.2, R53.1, U11.8 (FB)
VBUS: C101.1, C103.1, C106.1, U9.4 (IN), U10.1 (VIN), U10.2 (VIN), U11.1 (VIN), U11.2 (VIN), U11.3 (EN); also elsewhere on the board

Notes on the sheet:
ECONOMY
HIGH PERFORMANCE
R1 = R2*(VOUT/0.6v-1) VOUT = 1 R2 = 100k R1 = 100K*(1/0.6-1) R1 = 66666 (ACTUAL 66K5)
R1 = R2*(VOUT/0.6v-1) VOUT = 2.5 R2 = 100k R1 = 100K*(2.5/0.6-1) R1 = 316666 (ACTUAL 316K

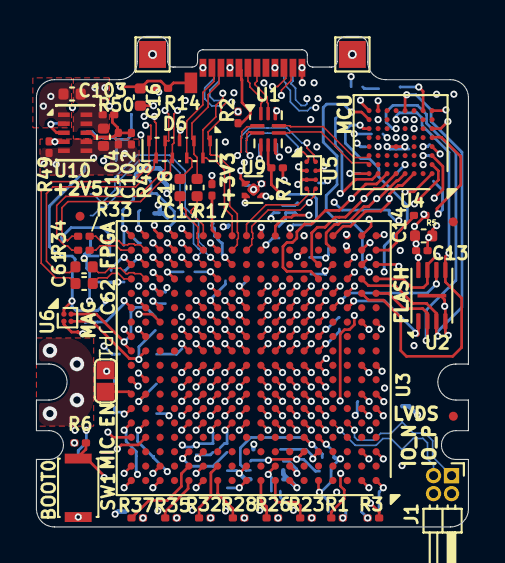
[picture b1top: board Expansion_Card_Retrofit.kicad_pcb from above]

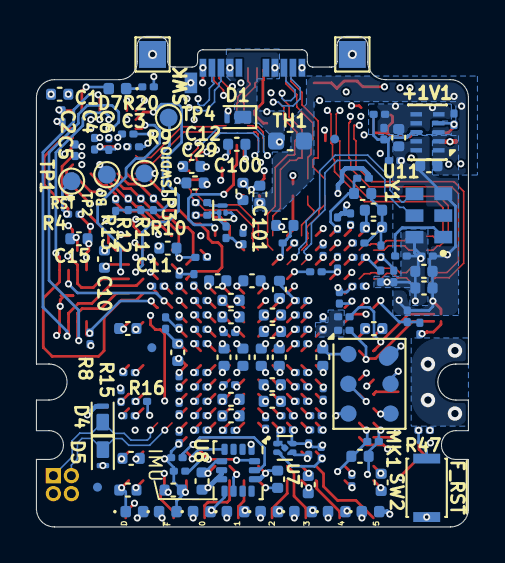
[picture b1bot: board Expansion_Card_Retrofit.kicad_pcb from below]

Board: 8 copper layers, 24.0 x 27.3 mm, 207 parts (160 on the bottom side), 105 nets.
